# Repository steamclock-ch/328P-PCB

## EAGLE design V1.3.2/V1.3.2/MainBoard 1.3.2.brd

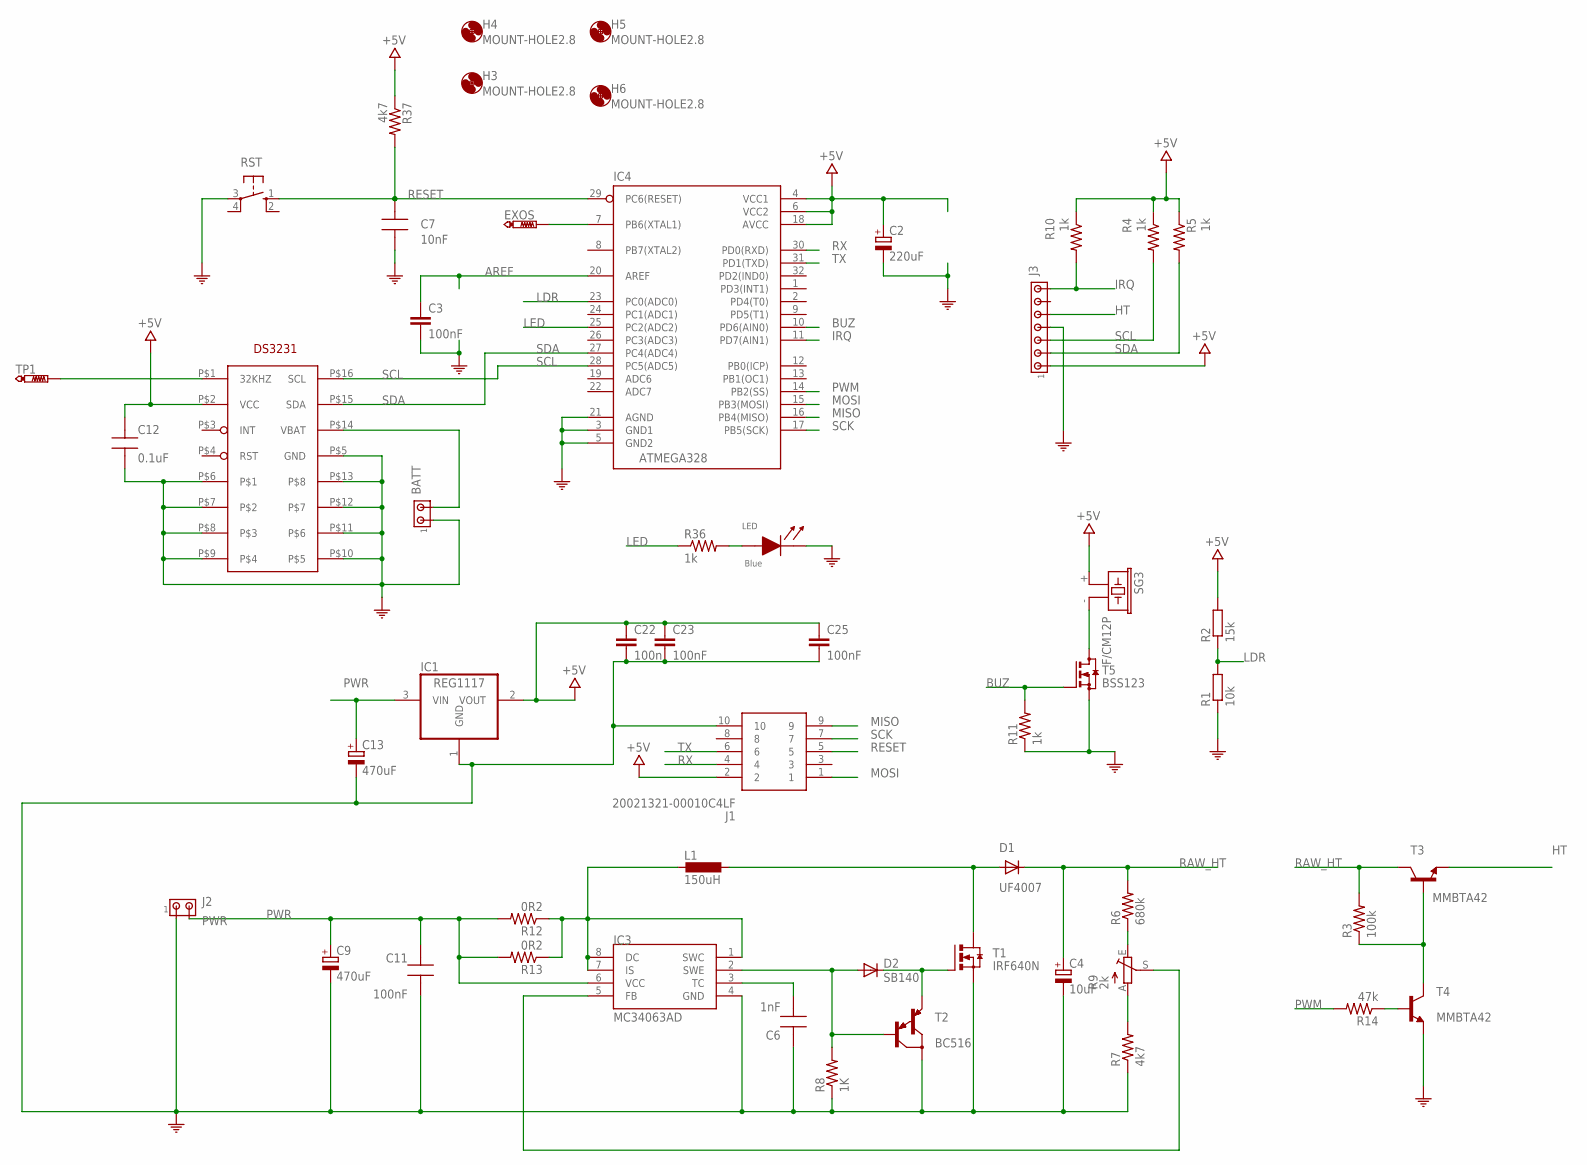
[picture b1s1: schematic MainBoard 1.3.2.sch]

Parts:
BATT: MTA02-100; 10X02MTA
C2: 220uF; SMC_D
C3, C23, C25: 100nF; C0603
C4: 10uF; E3,5-10
C6: 1nF; CAP0805-NP
C7: 10nF; CAP0805-NP
C9, C13: 470uF; SMC_D
C11: 100nF; CAP0805-NP
C12: 0.1uF; CAP0805-NP
C22: 100n; C0603
D1: UF4007; F126-10
D2: SB140; DO07
EXOS: PTR1TP09R; TP09R
H3, H4, H5, H6: MOUNT-HOLE2.8; 2,8
IC1: REG1117; SOT223
IC3: MC34063AD; SOIC8
IC4: ATMEGA328; QFP032
IC5: DS3231SPIC16W; SOIC-16W; MOUSER 700-DS3231S#
J1: 20021321-00010C4LF; 2002132100010C4LF
J2: PWR; 10X02MTA
J3: MTA07-100; 10X07MTA
L1: 150uH; D0522P; MOUSER 994-DO5022P-154MLB
LED: Blue; LED0805
R1: 10k; M2012
R2: 15k; 0204V
R3: 100k; R2012
R4, R5, R10, R11, R36: 1k; M2012
R6: 680k; R2012
R7: 4k7; R2012
R8: 1K; R2012
R9: 2k; B25P
R12, R13: 0R2; R2010
R14: 47k; R2012
R37: 4k7; M2012
RST: 10-XX; B3F-10XX
SG3: F/CM12P
T1: IRF640N; D2PACK; MOUSER 942-IRF640NSTRLPBF
T2: BC516; TO92
T3, T4: MMBTA42; SOT23
T5: BSS123; SOT23; MOUSER 512-BSS123
TP1: PTR1TP09R; TP09R

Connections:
+5V: C2.+, C12.1, C22.1, C23.1, C25.1, IC1.2 (VOUT), IC4.4 (VCC1), IC4.6 (VCC2), IC4.18 (AVCC), IC5.P$2 (VCC), J1.2, J3.1, R2.2, R4.1, R5.1, R10.1, R37.1, SG3.+ (1)
AREF: C3.1, IC4.20 (AREF)
BATT: BATT.2, IC5.P$14 (VBAT)
BUZ: IC4.10 (PD6(AIN0)), R11.2, T5.1 (G)
GND: BATT.1, C2.-, C3.2, C4.-, C6.1, C7.2, C9.-, C11.1, C12.2, C13.-, C22.2, C23.2, C25.2, IC1.1 (GND), IC3.4 (GND), IC4.3 (GND1), IC4.5 (GND2), IC4.21 (AGND), IC5.P$5 (GND), IC5.P$6, IC5.P$7, IC5.P$8, IC5.P$9, IC5.P$10, IC5.P$11, IC5.P$12, IC5.P$13, J1.10, J2.1, J3.4, LED.1 (CA), R1.1, R7.1, R8.1, R11.1, RST.3, T1.3 (S), T2.3 (C), T4.2 (E), T5.2 (S)
HT: J3.5, T3.2 (E)
IRQ: IC4.11 (PD7(AIN1)), J3.7, R10.2
LDR: IC4.23 (PC0(ADC0)), R1.2, R2.1
LED: IC4.25 (PC2(ADC2)), R36.1
MISO: IC4.16 (PB4(MISO)), J1.9
MOSI: IC4.15 (PB3(MOSI)), J1.1
unnamed: IC5.P$1 (32KHZ), TP1.TP
unnamed: D1.A, L1.P$2 (2), T1.2 (D)
unnamed: SG3.- (2), T5.3 (D)
unnamed: EXOS.TP, IC4.7 (PB6(XTAL1))
unnamed: C6.2, IC3.3 (TC)
unnamed: R3.1, T3.1 (B), T4.3 (C)
unnamed: R7.2, R9.A
unnamed: D2.A, IC3.2 (SWE), R8.2, T2.2 (B)
unnamed: R6.1, R9.E
unnamed: LED.2 (AN), R36.2
unnamed: IC3.5 (FB), R9.S
unnamed: IC3.1 (SWC), IC3.7 (IS), IC3.8 (DC), L1.P$1 (1), R12.1, R13.1
unnamed: R14.1, T4.1 (B)
unnamed: D2.C, T1.1 (G), T2.1 (E)
PWM: IC4.14 (PB2(SS)), R14.2
PWR: C9.+, C11.2, C13.+, IC1.3 (VIN), IC3.6 (VCC), J2.2, R12.2, R13.2
RAW_HT: C4.+, D1.C, R3.2, R6.2, T3.3 (C)
RESET: C7.1, IC4.29 (PC6(RESET)), J1.5, R37.2, RST.1 (S)
RX: IC4.30 (PD0(RXD)), J1.4
SCK: IC4.17 (PB5(SCK)), J1.7
SCL: IC4.28 (PC5(ADC5)), IC5.P$16 (SCL), J3.3, R4.2
SDA: IC4.27 (PC4(ADC4)), IC5.P$15 (SDA), J3.2, R5.2
TX: IC4.31 (PD1(TXD)), J1.6

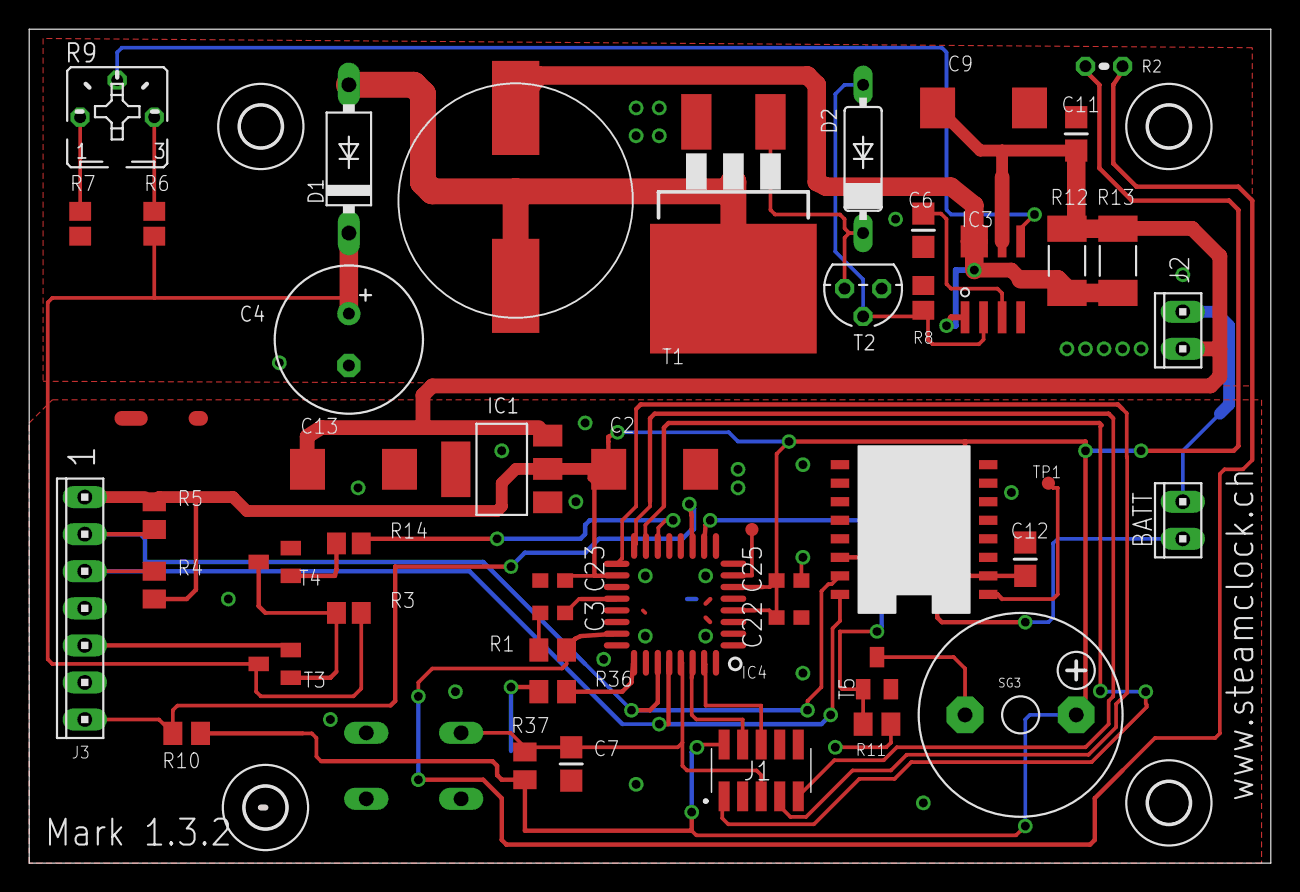
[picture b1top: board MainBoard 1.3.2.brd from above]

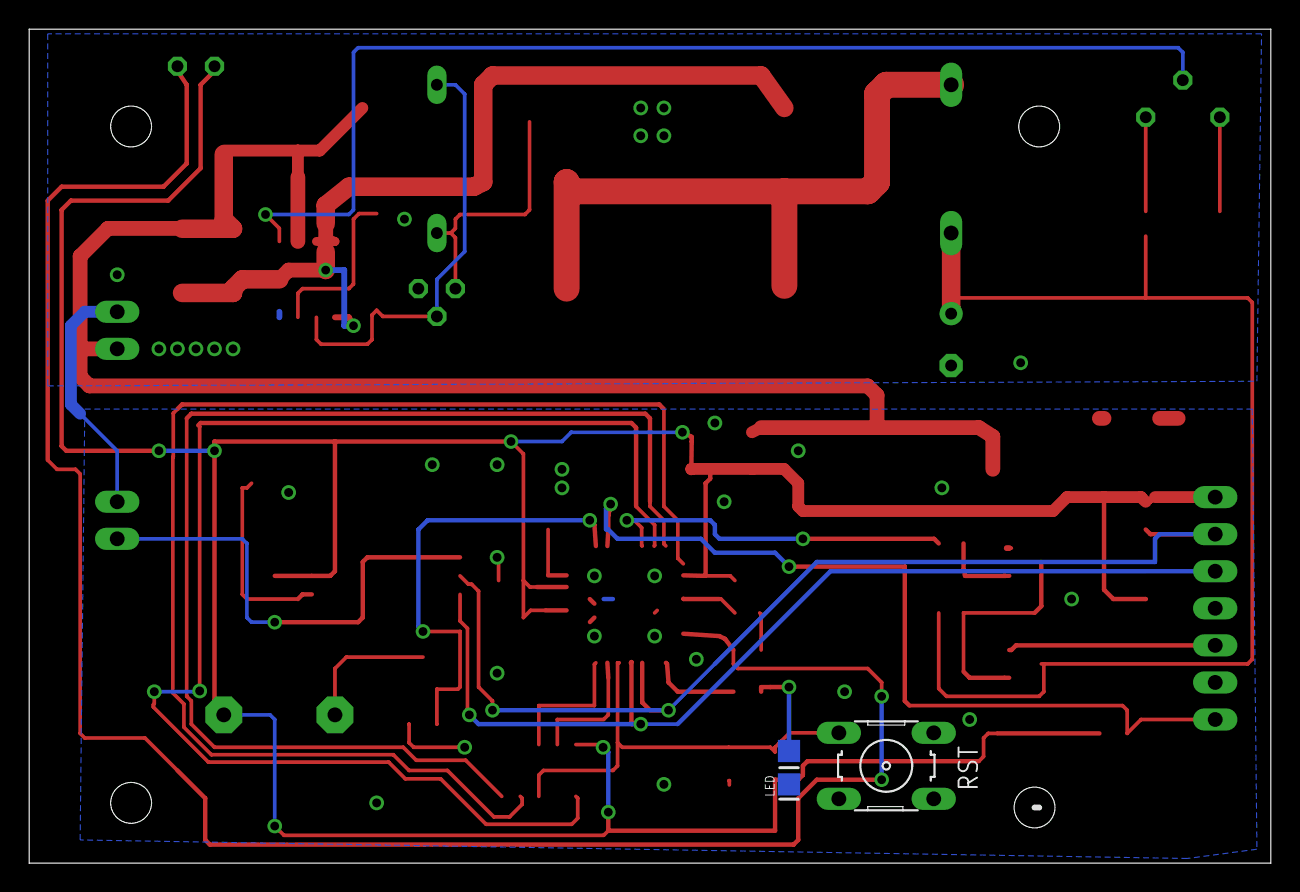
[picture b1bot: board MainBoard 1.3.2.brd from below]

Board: 2 copper layers, 85.1 x 57.1 mm, 53 parts (2 on the bottom side), 34 nets.

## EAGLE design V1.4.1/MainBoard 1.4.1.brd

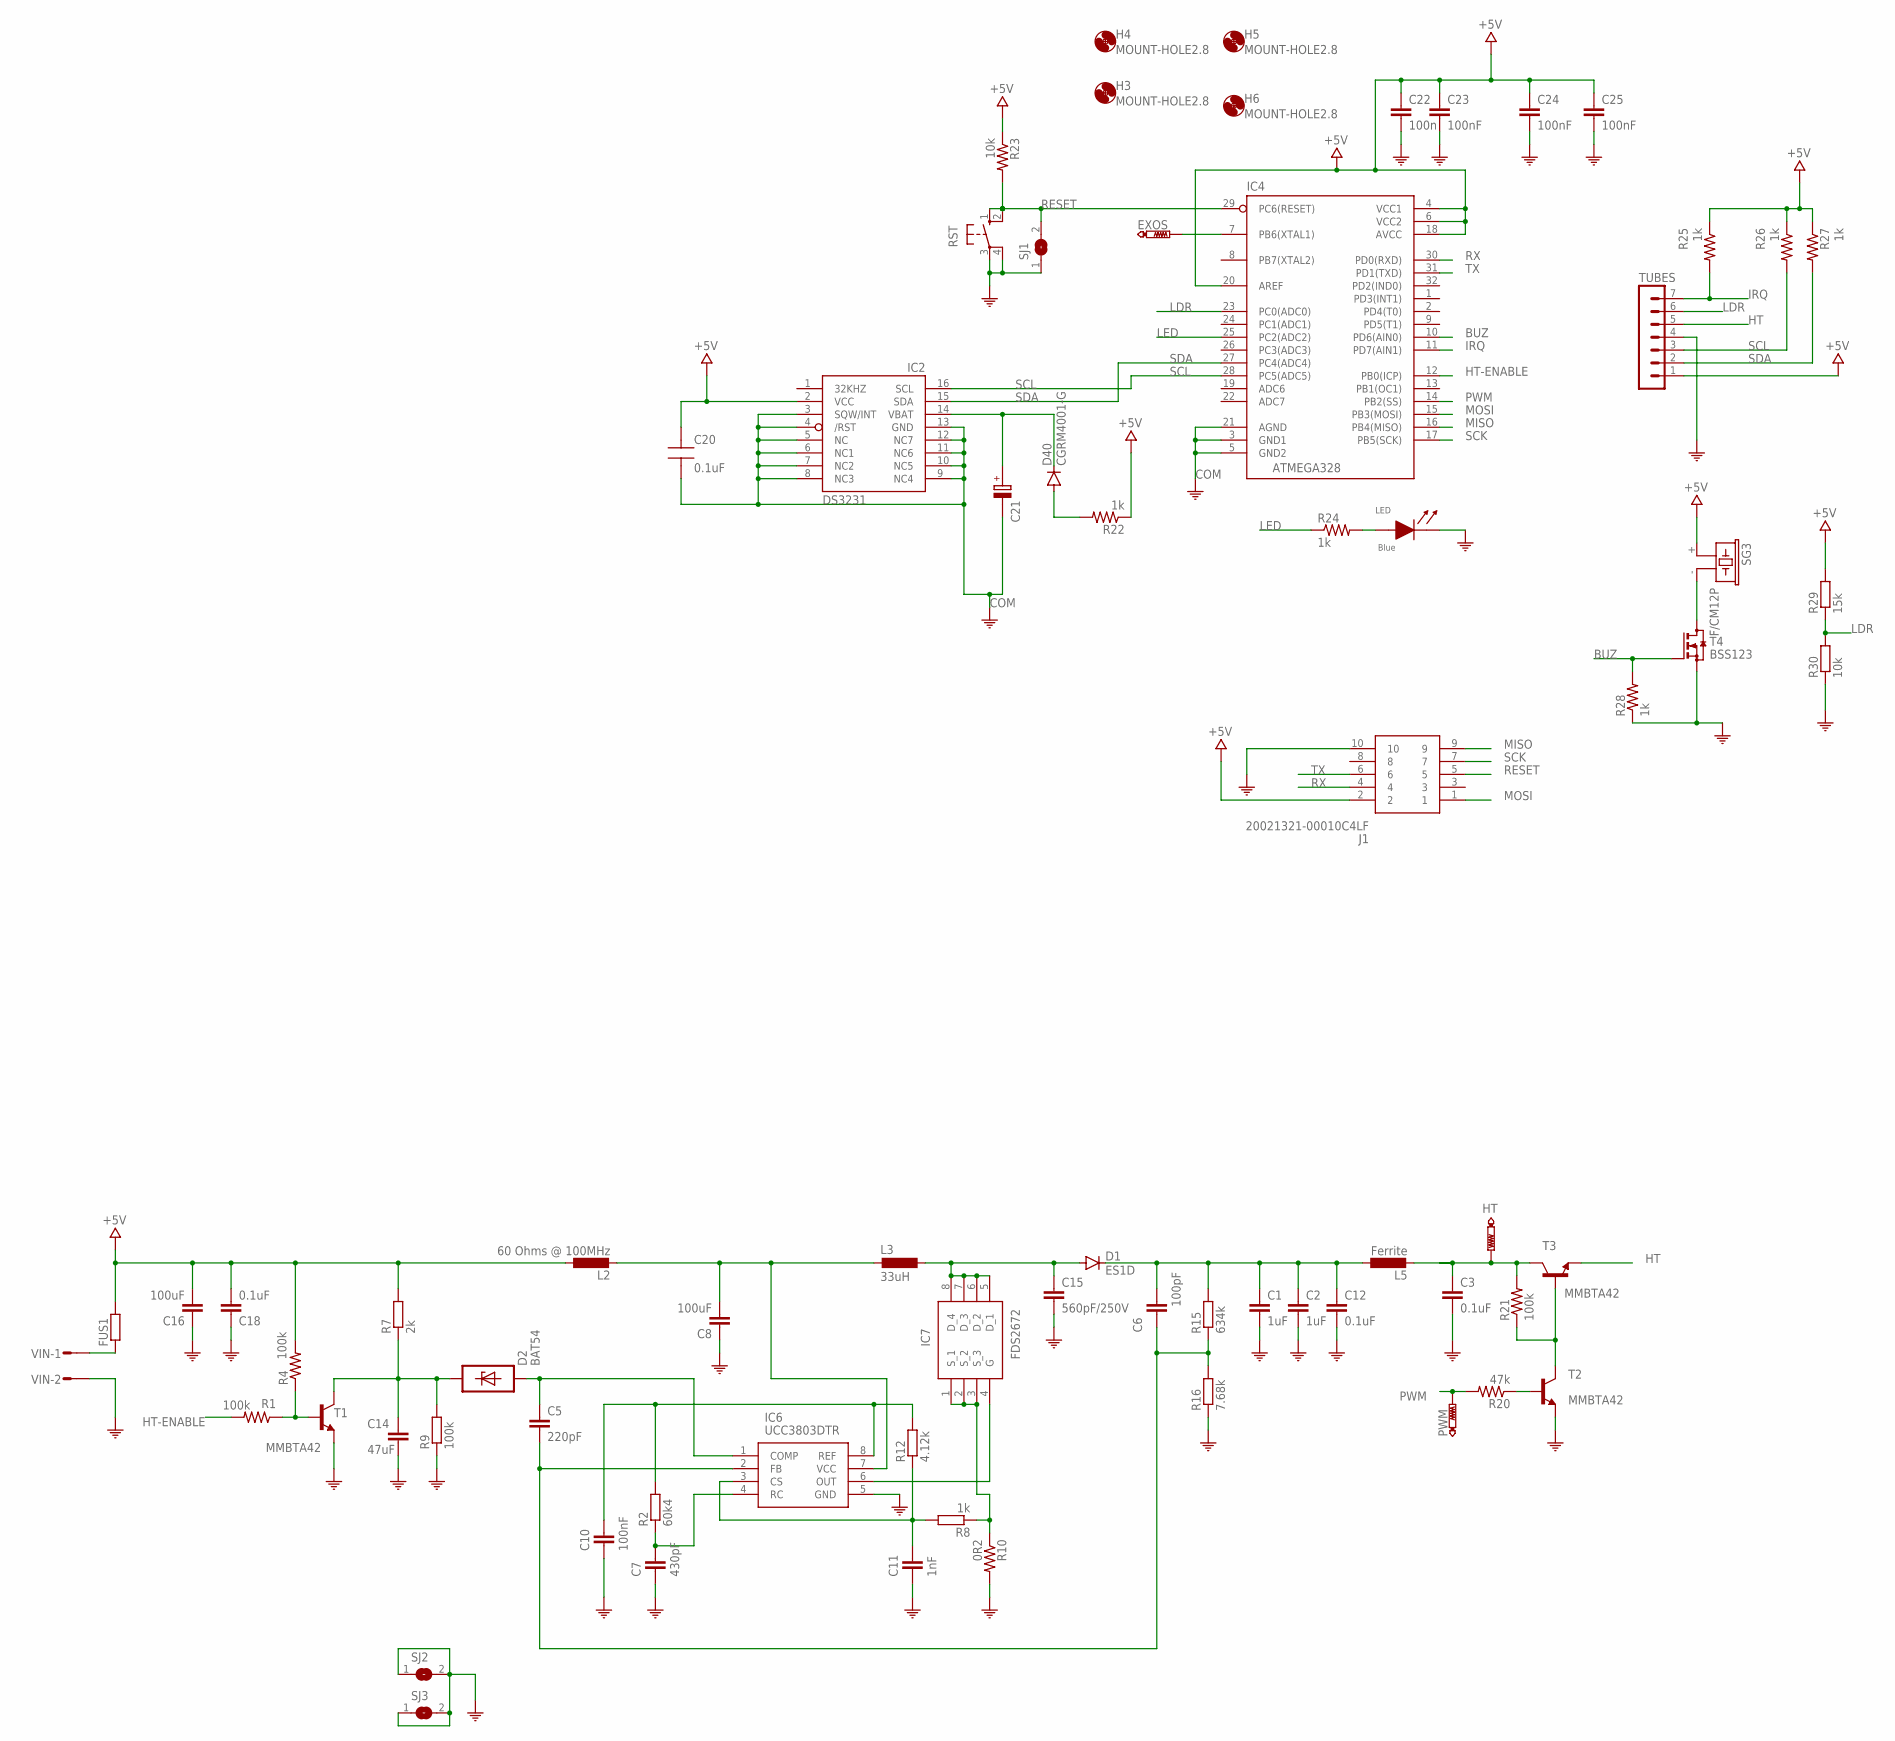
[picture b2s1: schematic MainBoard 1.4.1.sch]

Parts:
C1, C2: 1uF; C1812K; MOUSER 810-C4532X7T2E105MST
C3, C12: 0.1uF; C1808; MOUSER 80-CAN17C104KARACTU
C5: 220pF; C0805K
C6: 100pF; C0805; MOUSER 791-0603X106K100CT
C7: 430pF; C0805; MOUSER 791-0603X106K100CT
C8, C16: 100uF; C1210; MOUSER 963-EMK325ABJ107MM-P
C10: 100nF; C0805; MOUSER 791-0603X106K100CT
C11: 1nF; C0805; MOUSER 791-0603X106K100CT
C14: 47uF; C1210
C15: 560pF/250V; C0603
C18: 0.1uF; C0805
C20: 0.1uF; CAP0805-NP
C21: AHG-35/100-RADIAL; ELNA21.5X8.0; MOUSER 555-DB-5R5D474T
C22: 100n; C0603
C23, C24, C25: 100nF; C0603
D1: ES1D; SMB
D2: BAT54; SOD323
D40: CGRM4001-G; SOD-123_MINI-SMA; MOUSER 863-NSR0320MW2T1G
EXOS: PTR1TP09R; TP09R
FUS1: R-EU_R6332; R6332; MOUSER 530-0ZCG0150AF2C
H3, H4, H5, H6: MOUNT-HOLE2.8; 2,8
HT: PTR1TP09R; TP09R
IC2: DS3231/SO; SO16W
IC4: ATMEGA328; QFP032
IC6: UCC3803DTR; SOIC127P600X175-8N
IC7: FDS2672; SOIC127P600X175-8N
J1: 20021321-00010C4LF; 2002132100010C4LF
L2: 60 Ohms @ 100MHz; L2012C
L3: 33uH; MSS7341; MOUSER 710-784770330
L5: Ferrite; L2012C
LED: Blue; LED0805
PWM: PTR1TP09R; TP09R
R1, R4, R9: 100k; R0805
R2: 60k4; R0805
R7: 2k; R0805; MOUSER 754-RR1220P-202D
R8: 1k; R0805
R10: 0R2; R2010
R12: 4.12k; R0805; MOUSER 660-RN732ATD4121F100
R15: 634k; R0805; MOUSER 71-CRCW0603-634K-E3
R16: 7.68k; R0805; MOUSER 71-CRCW0805-7.68K-E3
R20: 47k; R2012
R21: 100k; R2012
R22, R24, R25, R26, R27, R28: 1k; M2012
R23, R30: 10k; M2012
R29: 15k; 0204V
RST: 10-XX; B3F-10XX
SG3: F/CM12P
SJ1, SJ2, SJ3: SJW
T1, T2, T3: MMBTA42; SOT23
T4: BSS123; SOT23
TUBES: MA07-1
VIN: M02S; 02P

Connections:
+5V: C16.2, C18.1, C20.1, C22.1, C23.1, C24.1, C25.1, FUS1.2, IC2.2 (VCC), IC4.4 (VCC1), IC4.6 (VCC2), IC4.18 (AVCC), IC4.20 (AREF), J1.2, L2.1, R4.2, R7.2, R22.1, R23.1, R25.1, R26.1, R27.1, R29.2, SG3.+ (1), TUBES.1
BATT: C21.+, D40.C, IC2.14 (VBAT)
BUZ: IC4.10 (PD6(AIN0)), R28.2, T4.1 (G)
COM: C1.2, C2.2, C3.2, C7.2, C8.1, C10.2, C11.2, C12.2, C14.2, C15.2, C16.1, C18.2, C20.2, C21.-, C22.2, C23.2, C24.2, C25.2, IC2.3 (SQW/INT), IC2.4 (/RST), IC2.5 (NC), IC2.6 (NC1), IC2.7 (NC2), IC2.8 (NC3), IC2.9 (NC4), IC2.10 (NC5), IC2.11 (NC6), IC2.12 (NC7), IC2.13 (GND), IC4.3 (GND1), IC4.5 (GND2), IC4.21 (AGND), IC6.5 (GND), J1.10, LED.1 (CA), R9.1, R10.2, R16.1, R28.1, R30.1, RST.3, RST.4 (P1), SJ1.1, SJ2.1, SJ2.2, SJ3.1, SJ3.2, T1.2 (E), T2.2 (E), T4.2 (S), TUBES.4, VIN.2
CS: C11.1, IC6.3 (CS), R8.2, R12.1
FB: C5.2, C6.2, IC6.2 (FB), R15.1, R16.2
HT: T3.2 (E), TUBES.5
HT-ENABLE: IC4.12 (PB0(ICP)), R1.2
IRQ: IC4.11 (PD7(AIN1)), R25.2, TUBES.7
LDR: IC4.23 (PC0(ADC0)), R29.1, R30.2, TUBES.6
LED: IC4.25 (PC2(ADC2)), R24.1
MISO: IC4.16 (PB4(MISO)), J1.9
MOSI: IC4.15 (PB3(MOSI)), J1.1
unnamed: SG3.- (2), T4.3 (D)
unnamed: EXOS.TP, IC4.7 (PB6(XTAL1))
unnamed: C1.1, C2.1, C6.1, C12.1, D1.C, L5.1, R15.2
unnamed: R21.1, T2.3 (C), T3.1 (B)
unnamed: R1.1, R4.1, T1.1 (B)
unnamed: C14.1, D2.C (1), R7.1, R9.2, T1.3 (C)
unnamed: C5.1, D2.A (2), IC6.1 (COMP)
unnamed: IC7.1 (S_1), IC7.2 (S_2), IC7.3 (S_3), R8.1, R10.1
unnamed: FUS1.1, VIN.1
unnamed: LED.2 (AN), R24.2
unnamed: C15.1, D1.A, IC7.5 (D_1), IC7.6 (D_2), IC7.7 (D_3), IC7.8 (D_4), L3.2
unnamed: R20.1, T2.1 (B)
unnamed: D40.A, R22.2
OUT: IC6.6 (OUT), IC7.4 (G)
PWM: IC4.14 (PB2(SS)), PWM.TP, R20.2
RAW_HT: C3.1, HT.TP, L5.2, R21.2, T3.3 (C)
RC: C7.1, IC6.4 (RC), R2.1
REF: C10.1, IC6.8 (REF), R2.2, R12.2
RESET: IC4.29 (PC6(RESET)), J1.5, R23.2, RST.1 (S), RST.2 (S1), SJ1.2
RX: IC4.30 (PD0(RXD)), J1.4
SCK: IC4.17 (PB5(SCK)), J1.7
SCL: IC2.16 (SCL), IC4.28 (PC5(ADC5)), R26.2, TUBES.3
SDA: IC2.15 (SDA), IC4.27 (PC4(ADC4)), R27.2, TUBES.2
TX: IC4.31 (PD1(TXD)), J1.6
VCC: C8.2, IC6.7 (VCC), L2.2, L3.1

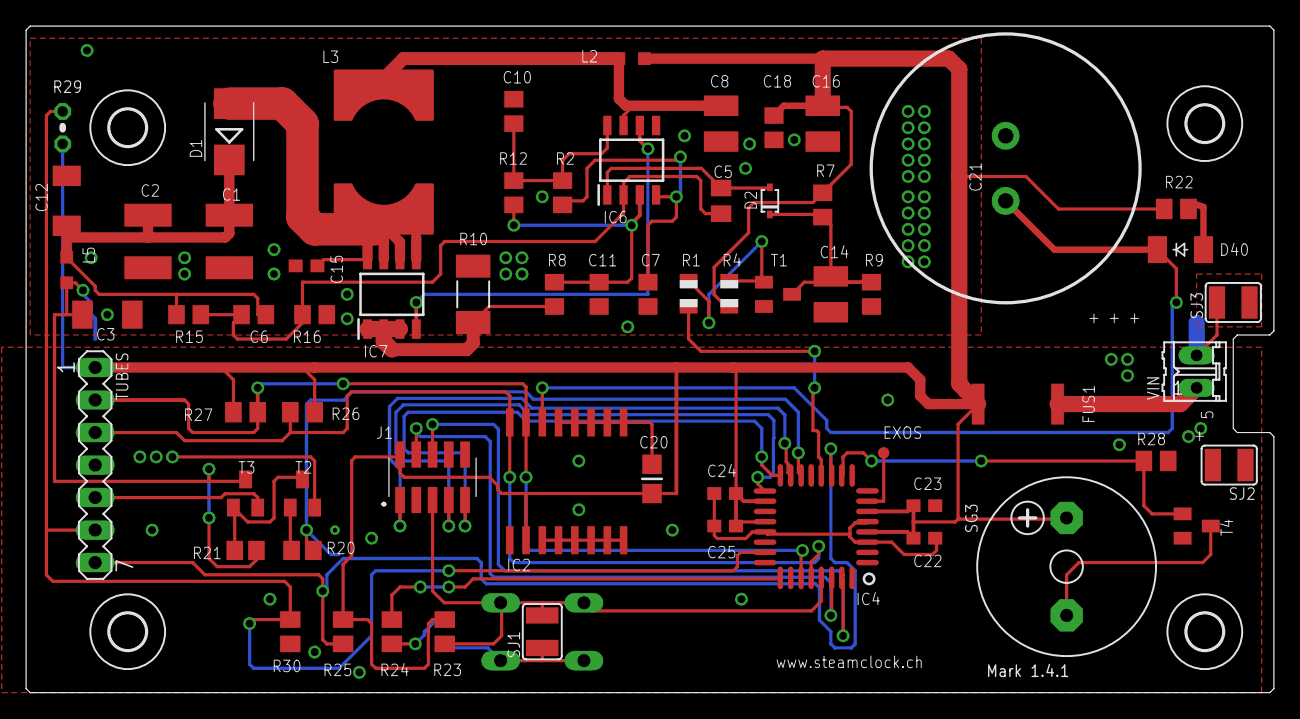
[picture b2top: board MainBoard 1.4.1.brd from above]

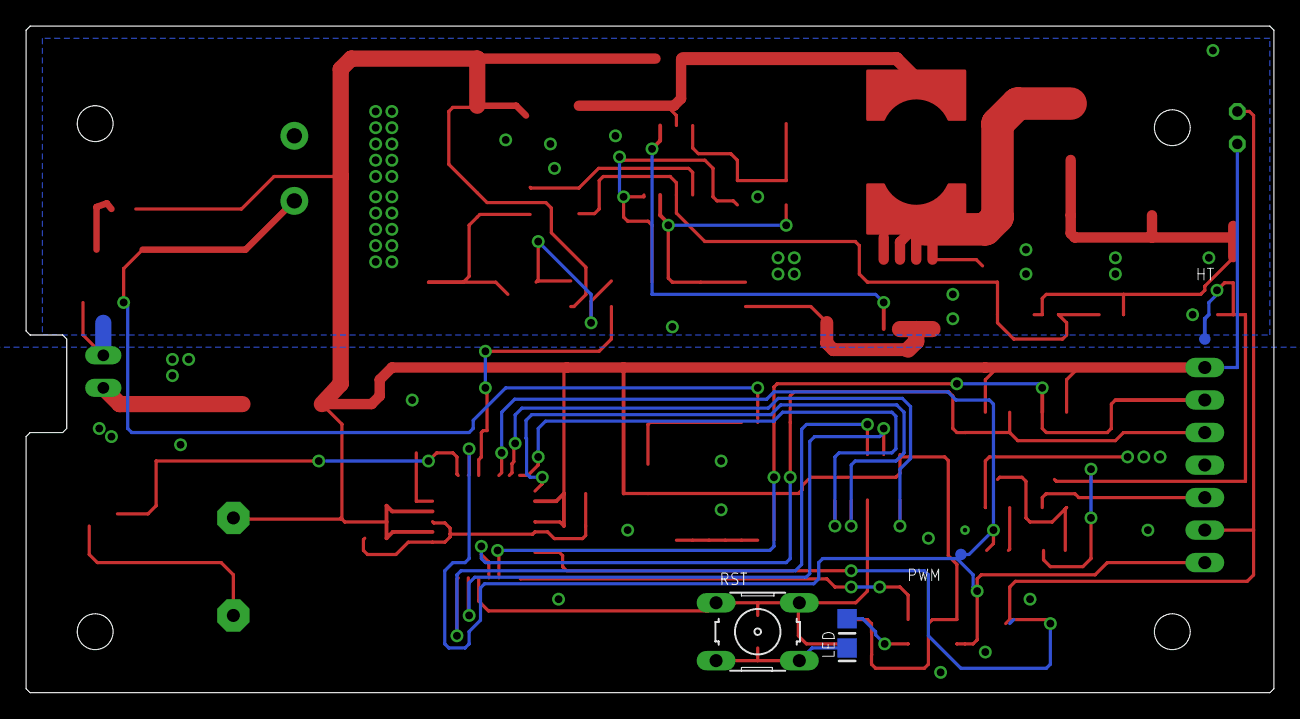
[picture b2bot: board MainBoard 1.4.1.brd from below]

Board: 2 copper layers, 97.5 x 52.1 mm, 72 parts (4 on the bottom side), 38 nets.

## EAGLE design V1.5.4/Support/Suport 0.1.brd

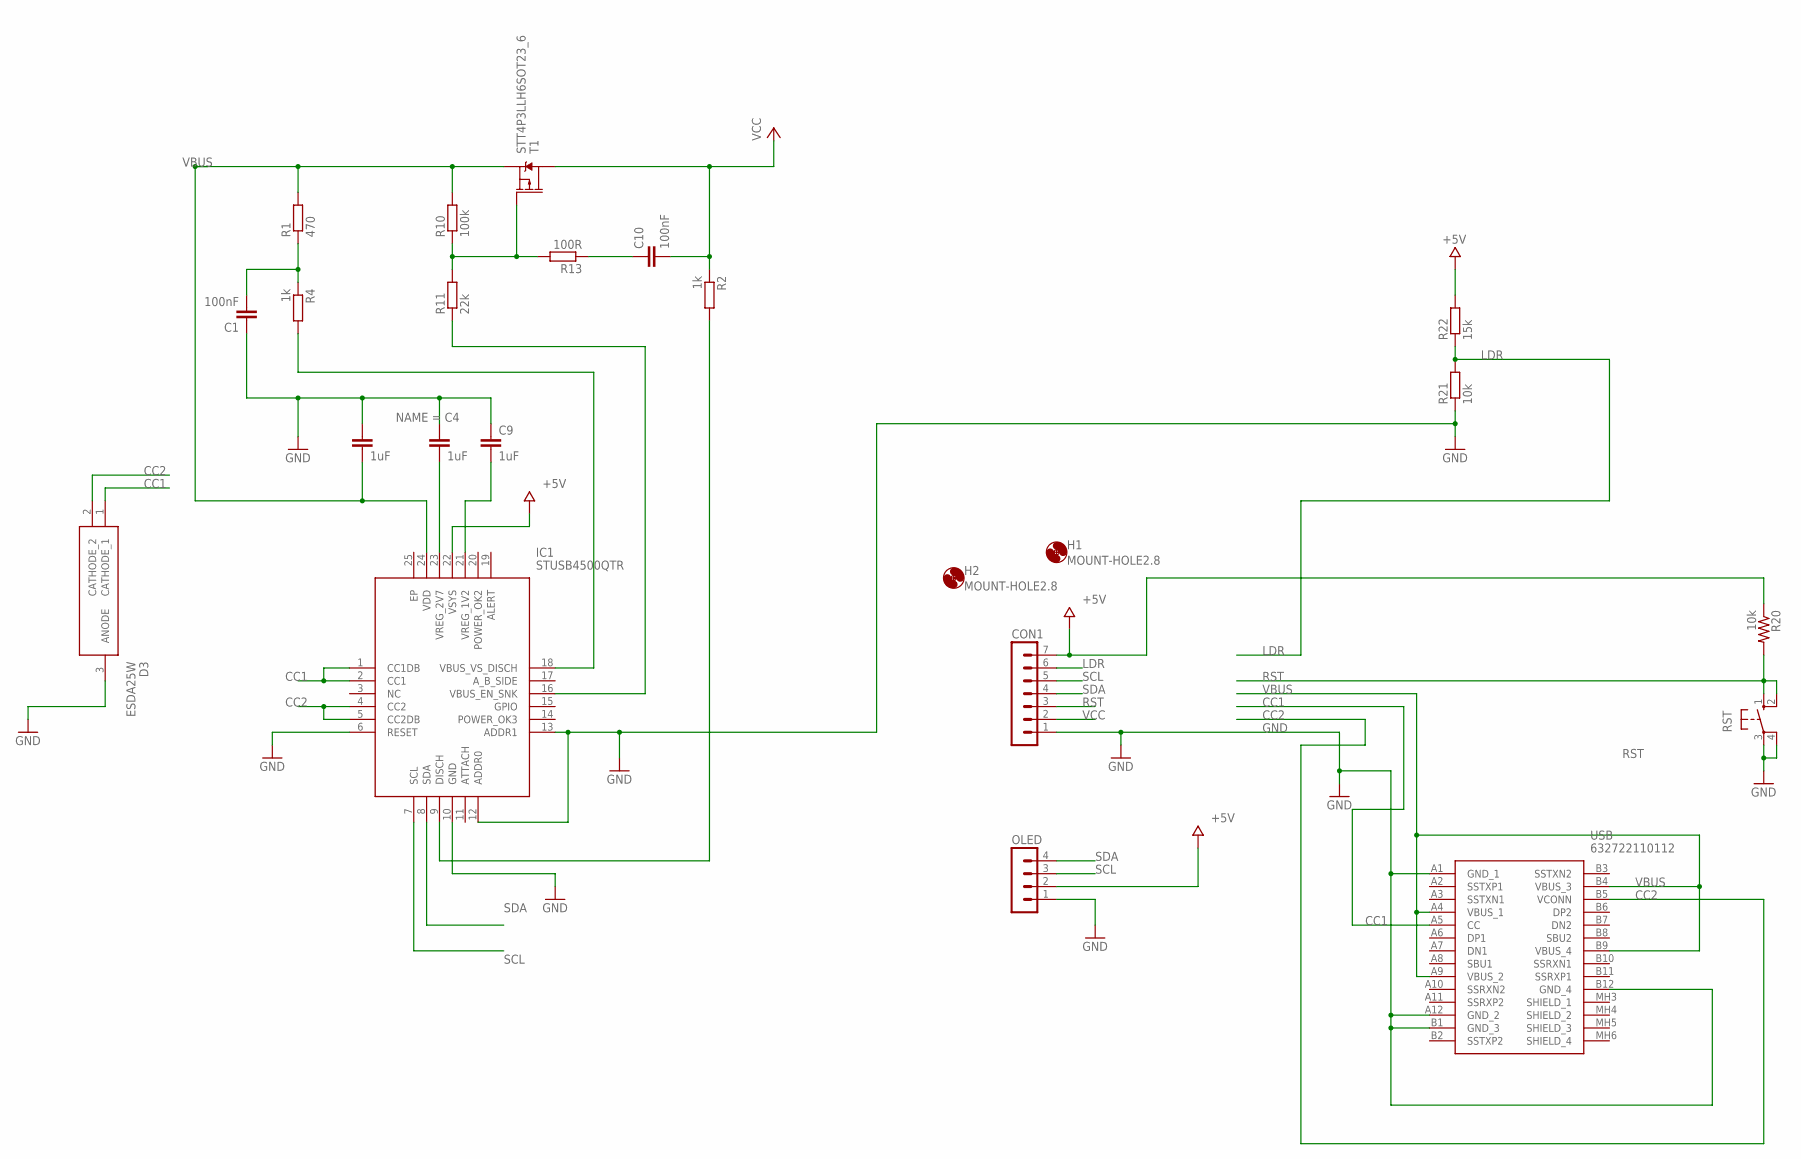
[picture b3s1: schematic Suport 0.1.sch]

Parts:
C1, C10: 100nF; C0402; MOUSER_PART_NUMBER 710-885012205050
C3, C4: 1uF; C0603; MOUSER_PART_NUMBER 81-GRM155R61E105KA2D
C9: 1uF; C0603
CON1: MA07-1
D3: ESDA25W; SOT65P210X110-3N
H1, H2: MOUNT-HOLE2.8; 2,8
IC1: STUSB4500QTR; QFN50P400X400X100-25N
OLED: MA04-1
R1: 470; R0805
R2, R4: 1k; R0805
R10: 100k; R0805
R11: 22k; R0805
R13: 100R; R0805
R20, R21: 10k; M0805
R22: 15k; 0204V
RST: 10-XX; B3F-10XX
T1: STT4P3LLH6SOT23_6; SOT23-6
USB: 632722110112

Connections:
+5V: CON1.7, IC1.22 (VSYS), OLED.2, R20.1, R22.2
CC1: D3.1 (CATHODE_1), IC1.1 (CC1DB), IC1.2 (CC1), USB.A5 (CC)
CC2: D3.2 (CATHODE_2), IC1.4 (CC2), IC1.5 (CC2DB), USB.B5 (VCONN)
GND: C1.1, C3.1, C4.1, C9.1, CON1.1, D3.3 (ANODE), IC1.6 (RESET), IC1.10 (GND), IC1.12 (ADDR0), IC1.13 (ADDR1), OLED.1, R21.1, RST.3, RST.4 (P1), USB.A1 (GND_1), USB.A12 (GND_2), USB.B1 (GND_3), USB.B12 (GND_4)
LDR: CON1.6, R21.2, R22.1
unnamed: C1.2, R1.1, R4.1
unnamed: R10.1, R11.2, R13.2, T1.3 (G)
unnamed: C10.1, R13.1
unnamed: IC1.16 (VBUS_EN_SNK), R11.1
unnamed: IC1.9 (DISCH), R2.2
unnamed: IC1.18 (VBUS_VS_DISCH), R4.2
RST: CON1.3, R20.2, RST.1 (S), RST.2 (S1)
SCL: CON1.5, IC1.7 (SCL), OLED.3
SDA: CON1.4, IC1.8 (SDA), OLED.4
VBUS: C3.2, IC1.24 (VDD), R1.2, R10.2, T1.4 (S), USB.A4 (VBUS_1), USB.A9 (VBUS_2), USB.B4 (VBUS_3), USB.B9 (VBUS_4)
VCC: C10.2, CON1.2, R2.1, T1.1 (D), T1.2 (D), T1.5 (D), T1.6 (D)
VREG_1V2: C9.2, IC1.21 (VREG_1V2)
VREG_2V7: C4.2, IC1.23 (VREG_2V7)

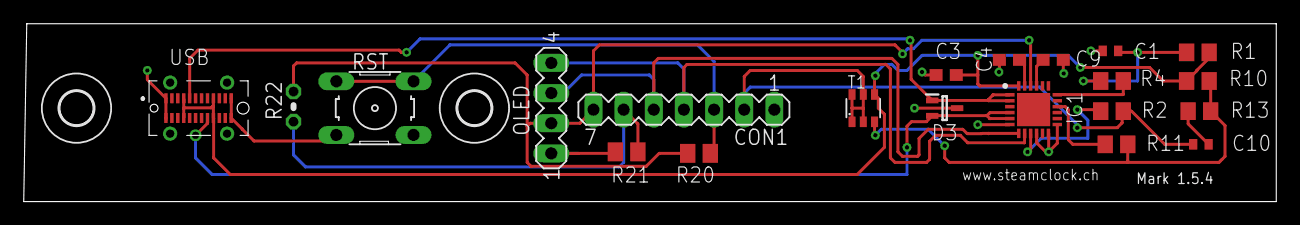
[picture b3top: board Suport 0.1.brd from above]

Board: 2 copper layers, 105.5 x 15.0 mm, 23 parts (0 on the bottom side), 18 nets.
